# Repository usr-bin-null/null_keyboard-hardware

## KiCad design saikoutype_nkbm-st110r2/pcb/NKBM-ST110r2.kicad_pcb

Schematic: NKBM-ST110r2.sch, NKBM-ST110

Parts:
H11: SPI
H21: EXPANSION
H31: RESET
H41: VCCIN
L00, L01, L02, L03, L04, L05, L06, L07, L08, L09: LED
MCU1: Teesny2.0++; TEENSY2.0++
R00, R01, R02, R03, R04, R05, R06, R07, R08, R09: 330
USB_POWER: SOLDER_JUMPER; SOLDER_BRIDGE

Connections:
/COL_00: MCU1.31 (PF0); also elsewhere on the board
/COL_01: MCU1.30 (PF1); also elsewhere on the board
/COL_02: MCU1.29 (PF2); also elsewhere on the board
/COL_03: MCU1.28 (PF3); also elsewhere on the board
/COL_04: MCU1.27 (PF4); also elsewhere on the board
/COL_05: MCU1.26 (FP5); also elsewhere on the board
/COL_06: MCU1.25 (FP6); also elsewhere on the board
/COL_07: MCU1.24 (PF7); also elsewhere on the board
/COL_08: MCU1.13 (PC0); also elsewhere on the board
/COL_09: MCU1.14 (PC1); also elsewhere on the board
/COL_10: MCU1.15 (PC2); also elsewhere on the board
/COL_11: MCU1.16 (PC3); also elsewhere on the board
/COL_12: MCU1.17 (PC4); also elsewhere on the board
/COL_13: MCU1.18 (PC5); also elsewhere on the board
/COL_14: MCU1.19 (PC6); also elsewhere on the board
/GND: L00.1 (K), L01.1 (K), L02.1 (K), L03.1 (K), L04.1 (K), L05.1 (K), L06.1 (K), L07.1 (K), L08.1 (K), L09.1 (K), MCU1.1 (GND), MCU1.22 (GND), MCU1.33 (GND); also elsewhere on the board
/LED_00: MCU1.2 (PB7), R00.1
/LED_01: MCU1.3 (PD0), R01.1
/LED_02: MCU1.4 (PD1), R02.1
/LED_03: MCU1.41 (PB5), R03.1
/LED_04: MCU1.40 (PB4), R04.1
/LED_05: MCU1.42 (PB6), R05.1
/LED_06: MCU1.7 (PD4), R06.1
/LED_07: MCU1.8 (PD5), R07.1
/LED_08: MCU1.9 (PD6), R08.1
/LED_09: MCU1.10 (PD7), R09.1
/MISO: MCU1.39 (PB3); also elsewhere on the board
/MOSI: MCU1.38 (PB2); also elsewhere on the board
/ROW_00: MCU1.44 (PA0); also elsewhere on the board
/ROW_01: MCU1.45 (PA1); also elsewhere on the board
/ROW_02: MCU1.46 (PA2); also elsewhere on the board
/ROW_03: MCU1.47 (PA3); also elsewhere on the board
/ROW_04: MCU1.48 (PA4); also elsewhere on the board
/ROW_05: MCU1.49 (PA5); also elsewhere on the board
/ROW_06: MCU1.50 (PA6); also elsewhere on the board
/ROW_07: MCU1.51 (PA7); also elsewhere on the board
/RST: MCU1.23 (RESET); also elsewhere on the board
/RX: MCU1.5 (PD2); also elsewhere on the board
/SCLK: MCU1.37 (PB1); also elsewhere on the board
/SELECT: MCU1.36 (PB0); also elsewhere on the board
/TX: MCU1.6 (PD3); also elsewhere on the board
/VCC: MCU1.43 (VCC); also elsewhere on the board
/VCC1: MCU1.21 (VCC)
unnamed: L00.2 (A), R00.2
unnamed: L01.2 (A), R01.2
unnamed: L02.2 (A), R02.2
unnamed: L03.2 (A), R03.2
unnamed: L04.2 (A), R04.2
unnamed: L05.2 (A), R05.2
unnamed: L06.2 (A), R06.2
unnamed 161: L07.2 (A), R07.2; also elsewhere on the board
unnamed: L08.2 (A), R08.2
unnamed 163: L09.2 (A), R09.2; also elsewhere on the board
unnamed 164: MCU1.11 (PE0); also elsewhere on the board
unnamed 165: MCU1.12 (PE1); also elsewhere on the board

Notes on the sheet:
LED
DIODE
Component Orientation

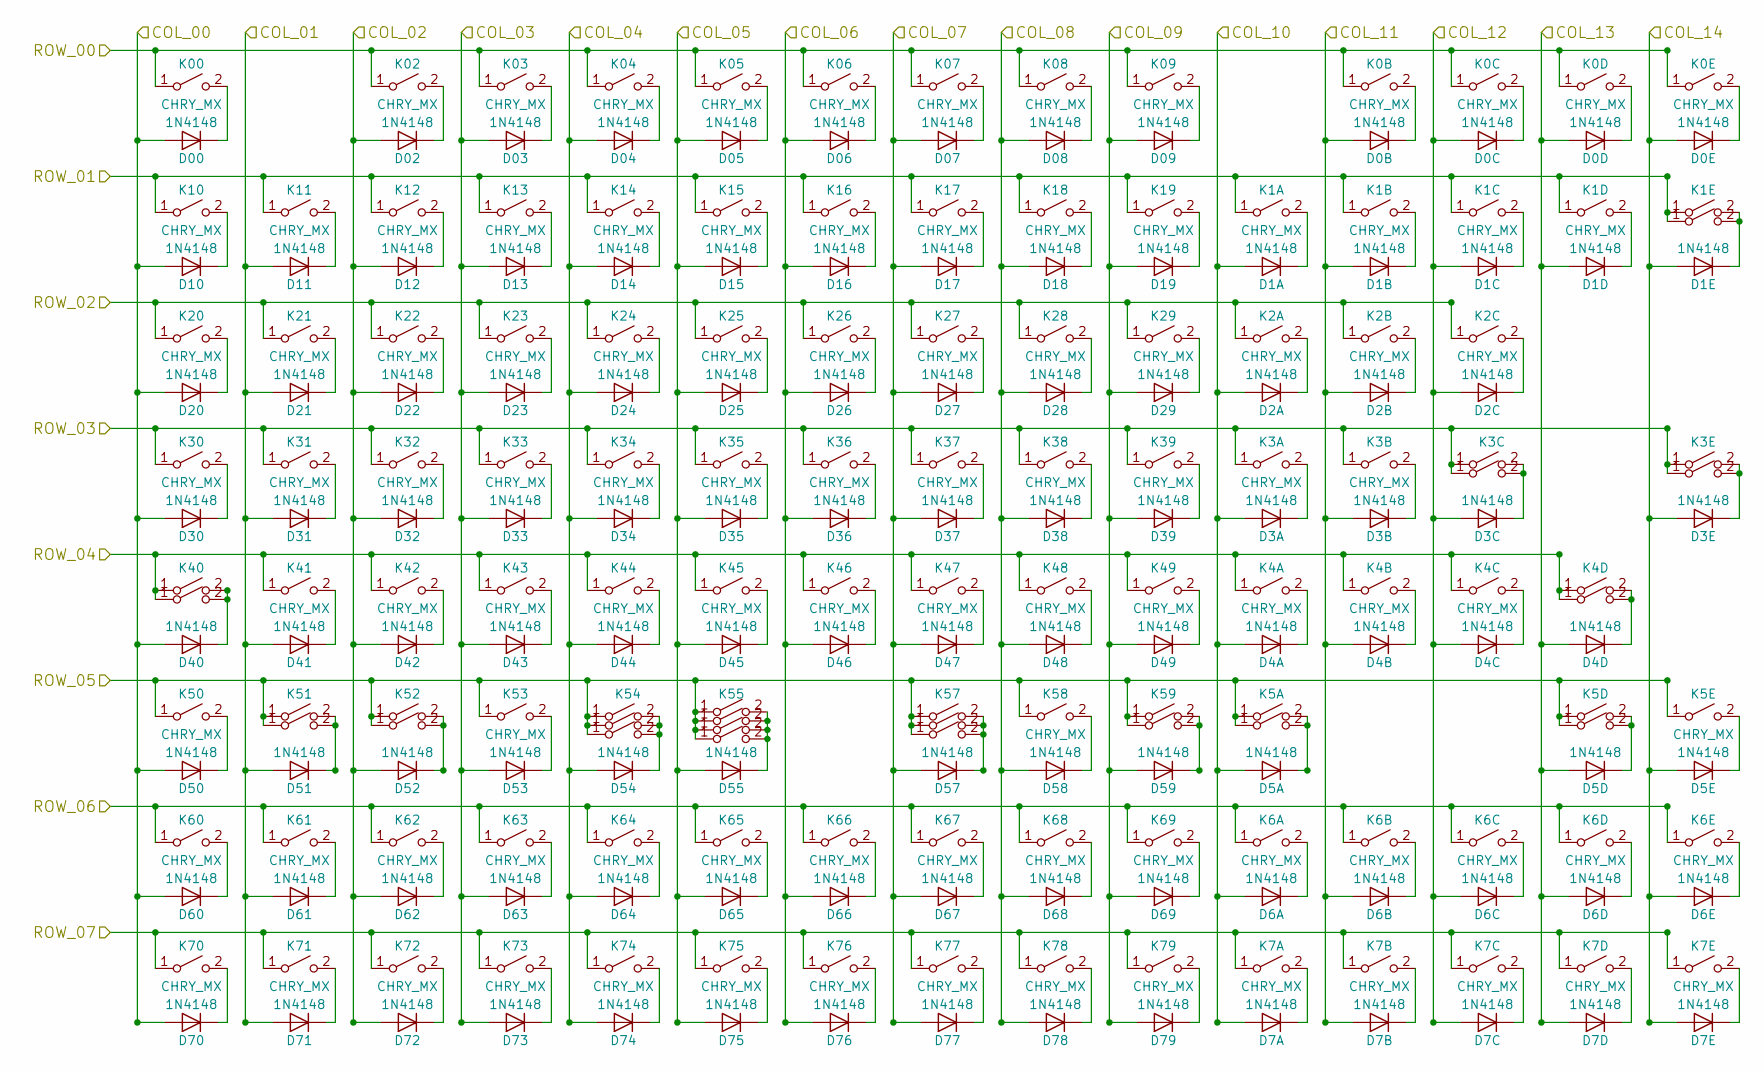
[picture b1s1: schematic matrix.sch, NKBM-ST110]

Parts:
D00, D0B, D0C, D0D, D0E, D1A, D1B, D1C, D1D, D1E, D02, D2A, D2B, D2C, D03, D3A, D3B, D3C, D3E, D04, D4A, D4B, D4C, D4D, D05, D5A, D5D, D5E, D06, D6A, D6B, D6C, D6D, D6E, D07, D7A, D7B, D7C, D7D, D7E, D08, D09, D10, D11, D12, D13, D14, D15, D16, D17, D18, D19, D20, D21, D22, D23, D24, D25, D26, D27, D28, D29, D30, D31, D32, D33, D34, D35, D36, D37, D38, D39, D40, D41, D42, D43, D44, D45, D46, D47, D48, D49, D50, D51, D52, D53, D54, D55, D57, D58, D59, D60, D61, D62, D63, D64, D65, D66, D67, D68, D69, D70, D71, D72, D73, D74, D75, D76, D77, D78, D79: 1N4148; DIODE
K00, K0B, K0C, K0D, K0E, K1A, K1B, K1C, K1D, K1E1, K02, K2A, K2B, K2C, K03, K3A, K3B, K04, K4A, K4B, K4C, K05, K5D, K06, K6A, K6B, K6C, K6D, K6E, K07, K7A, K7B, K7C, K7D, K7E, K08, K09, K10, K11, K12, K13, K14, K15, K16, K17, K18, K19, K21, K22, K23, K24, K25, K26, K27, K28, K29, K31, K32, K33, K34, K35, K36, K37, K38, K39, K41, K42, K43, K44, K46, K47, K48, K49, K51, K53, K60, K61, K62, K63, K64, K65, K66, K67, K68, K69, K70, K71, K72, K73, K74, K75, K76, K77, K78, K79: CHRY_MX; CHERRY_PLATE_100H
K1E, K3E, K54, K57: CHRY_MX; CHERRY_PLATE_200H
K3C, K3C1, K20: CHRY_MX; CHERRY_PLATE_150H
K3E1, K40, K541, K572: CHRY_MX; CHERRY_PLATE_225H
K4D, K30: CHRY_MX; CHERRY_PLATE_175H
K4D2: CHRY_MX; CHERRY_PLATE_275H
K5A, K5A1, K5D1, K5E, K45, K50, K52, K58, K59, K401, K511, K521, K542, K551, K553, K571, K591: CHRY_MX; CHERRY_PLATE_125H
K55: CHRY_MX; CHERRY_PLATE_625H
K552: CHRY_MX; CHERRY_PLATE_450H

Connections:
/COL_00: D00.2 (A), D10.2 (A), D20.2 (A), D30.2 (A), D40.2 (A), D50.2 (A), D60.2 (A), D70.2 (A); also elsewhere on the board
/COL_01: D11.2 (A), D21.2 (A), D31.2 (A), D41.2 (A), D51.2 (A), D61.2 (A), D71.2 (A); also elsewhere on the board
/COL_02: D02.2 (A), D12.2 (A), D22.2 (A), D32.2 (A), D42.2 (A), D52.2 (A), D62.2 (A), D72.2 (A); also elsewhere on the board
/COL_03: D03.2 (A), D13.2 (A), D23.2 (A), D33.2 (A), D43.2 (A), D53.2 (A), D63.2 (A), D73.2 (A); also elsewhere on the board
/COL_04: D04.2 (A), D14.2 (A), D24.2 (A), D34.2 (A), D44.2 (A), D54.2 (A), D64.2 (A), D74.2 (A); also elsewhere on the board
/COL_05: D05.2 (A), D15.2 (A), D25.2 (A), D35.2 (A), D45.2 (A), D55.2 (A), D65.2 (A), D75.2 (A); also elsewhere on the board
/COL_06: D06.2 (A), D16.2 (A), D26.2 (A), D36.2 (A), D46.2 (A), D66.2 (A), D76.2 (A); also elsewhere on the board
/COL_07: D07.2 (A), D17.2 (A), D27.2 (A), D37.2 (A), D47.2 (A), D57.2 (A), D67.2 (A), D77.2 (A); also elsewhere on the board
/COL_08: D08.2 (A), D18.2 (A), D28.2 (A), D38.2 (A), D48.2 (A), D58.2 (A), D68.2 (A), D78.2 (A); also elsewhere on the board
/COL_09: D09.2 (A), D19.2 (A), D29.2 (A), D39.2 (A), D49.2 (A), D59.2 (A), D69.2 (A), D79.2 (A); also elsewhere on the board
/COL_10: D1A.2 (A), D2A.2 (A), D3A.2 (A), D4A.2 (A), D5A.2 (A), D6A.2 (A), D7A.2 (A); also elsewhere on the board
/COL_11: D0B.2 (A), D1B.2 (A), D2B.2 (A), D3B.2 (A), D4B.2 (A), D6B.2 (A), D7B.2 (A); also elsewhere on the board
/COL_12: D0C.2 (A), D1C.2 (A), D2C.2 (A), D3C.2 (A), D4C.2 (A), D6C.2 (A), D7C.2 (A); also elsewhere on the board
/COL_13: D0D.2 (A), D1D.2 (A), D4D.2 (A), D5D.2 (A), D6D.2 (A), D7D.2 (A); also elsewhere on the board
/COL_14: D0E.2 (A), D1E.2 (A), D3E.2 (A), D5E.2 (A), D6E.2 (A), D7E.2 (A); also elsewhere on the board
/ROW_00: K00.1 (A), K0B.1 (A), K0C.1 (A), K0D.1 (A), K0E.1 (A), K02.1 (A), K03.1 (A), K04.1 (A), K05.1 (A), K06.1 (A), K07.1 (A), K08.1 (A), K09.1 (A); also elsewhere on the board
/ROW_01: K1A.1 (A), K1B.1 (A), K1C.1 (A), K1D.1 (A), K1E.1 (A), K1E1.1 (A), K10.1 (A), K11.1 (A), K12.1 (A), K13.1 (A), K14.1 (A), K15.1 (A), K16.1 (A), K17.1 (A), K18.1 (A), K19.1 (A); also elsewhere on the board
/ROW_02: K2A.1 (A), K2B.1 (A), K2C.1 (A), K20.1 (A), K21.1 (A), K22.1 (A), K23.1 (A), K24.1 (A), K25.1 (A), K26.1 (A), K27.1 (A), K28.1 (A), K29.1 (A); also elsewhere on the board
/ROW_03: K3A.1 (A), K3B.1 (A), K3C.1 (A), K3C1.1 (A), K3E.1 (A), K3E1.1 (A), K30.1 (A), K31.1 (A), K32.1 (A), K33.1 (A), K34.1 (A), K35.1 (A), K36.1 (A), K37.1 (A), K38.1 (A), K39.1 (A); also elsewhere on the board
/ROW_04: K4A.1 (A), K4B.1 (A), K4C.1 (A), K4D.1 (A), K4D2.1 (A), K40.1 (A), K41.1 (A), K42.1 (A), K43.1 (A), K44.1 (A), K45.1 (A), K46.1 (A), K47.1 (A), K48.1 (A), K49.1 (A), K401.1 (A); also elsewhere on the board
/ROW_05: K5A.1 (A), K5A1.1 (A), K5D.1 (A), K5D1.1 (A), K5E.1 (A), K50.1 (A), K51.1 (A), K52.1 (A), K53.1 (A), K54.1 (A), K55.1 (A), K57.1 (A), K58.1 (A), K59.1 (A), K511.1 (A), K521.1 (A), K541.1 (A), K542.1 (A), K551.1 (A), K552.1 (A), K553.1 (A), K571.1 (A), K572.1 (A), K591.1 (A); also elsewhere on the board
/ROW_06: K6A.1 (A), K6B.1 (A), K6C.1 (A), K6D.1 (A), K6E.1 (A), K60.1 (A), K61.1 (A), K62.1 (A), K63.1 (A), K64.1 (A), K65.1 (A), K66.1 (A), K67.1 (A), K68.1 (A), K69.1 (A); also elsewhere on the board
/ROW_07: K7A.1 (A), K7B.1 (A), K7C.1 (A), K7D.1 (A), K7E.1 (A), K70.1 (A), K71.1 (A), K72.1 (A), K73.1 (A), K74.1 (A), K75.1 (A), K76.1 (A), K77.1 (A), K78.1 (A), K79.1 (A); also elsewhere on the board
unnamed: D0B.1 (K), K0B.2 (B)
unnamed: D0C.1 (K), K0C.2 (B)
unnamed: D0D.1 (K), K0D.2 (B)
unnamed: D0E.1 (K), K0E.2 (B)
unnamed: D00.1 (K), K00.2 (B)
unnamed: D1A.1 (K), K1A.2 (B)
unnamed: D1B.1 (K), K1B.2 (B)
unnamed: D1C.1 (K), K1C.2 (B)
unnamed: D1D.1 (K), K1D.2 (B)
unnamed 52: D1E.1 (K), K1E.2 (B), K1E1.2 (B); also elsewhere on the board
unnamed: D2A.1 (K), K2A.2 (B)
unnamed: D2B.1 (K), K2B.2 (B)
unnamed: D2C.1 (K), K2C.2 (B)
unnamed: D3A.1 (K), K3A.2 (B)
unnamed: D3B.1 (K), K3B.2 (B)
unnamed 58: D3C.1 (K), K3C.2 (B), K3C1.2 (B); also elsewhere on the board
unnamed 59: D3E.1 (K), K3E.2 (B), K3E1.2 (B); also elsewhere on the board
unnamed: D4A.1 (K), K4A.2 (B)
unnamed: D4B.1 (K), K4B.2 (B)
unnamed: D4C.1 (K), K4C.2 (B)
unnamed: D4D.1 (K), K4D.2 (B), K4D2.2 (B)
unnamed: D5A.1 (K), K5A.2 (B), K5A1.2 (B)
unnamed: D5D.1 (K), K5D.2 (B), K5D1.2 (B)
unnamed: D5E.1 (K), K5E.2 (B)
unnamed: D6A.1 (K), K6A.2 (B)
unnamed: D6B.1 (K), K6B.2 (B)
unnamed: D6C.1 (K), K6C.2 (B)
unnamed: D6D.1 (K), K6D.2 (B)
unnamed: D6E.1 (K), K6E.2 (B)
unnamed: D7A.1 (K), K7A.2 (B)
unnamed: D7B.1 (K), K7B.2 (B)
unnamed: D7C.1 (K), K7C.2 (B)
unnamed: D7D.1 (K), K7D.2 (B)
unnamed: D7E.1 (K), K7E.2 (B)
unnamed: D02.1 (K), K02.2 (B)
unnamed: D03.1 (K), K03.2 (B)
unnamed: D04.1 (K), K04.2 (B)
unnamed: D05.1 (K), K05.2 (B)
unnamed: D06.1 (K), K06.2 (B)
unnamed: D07.1 (K), K07.2 (B)
unnamed: D08.1 (K), K08.2 (B)
unnamed: D09.1 (K), K09.2 (B)
unnamed: D10.1 (K), K10.2 (B)
unnamed: D11.1 (K), K11.2 (B)
unnamed: D12.1 (K), K12.2 (B)
unnamed: D13.1 (K), K13.2 (B)
unnamed: D14.1 (K), K14.2 (B)
unnamed: D15.1 (K), K15.2 (B)
unnamed: D16.1 (K), K16.2 (B)
unnamed: D17.1 (K), K17.2 (B)
unnamed: D18.1 (K), K18.2 (B)
unnamed: D19.1 (K), K19.2 (B)
unnamed: D20.1 (K), K20.2 (B)
unnamed: D21.1 (K), K21.2 (B)
unnamed: D22.1 (K), K22.2 (B)
unnamed: D23.1 (K), K23.2 (B)
unnamed: D24.1 (K), K24.2 (B)
unnamed: D25.1 (K), K25.2 (B)
unnamed: D26.1 (K), K26.2 (B)
unnamed: D27.1 (K), K27.2 (B)
unnamed: D28.1 (K), K28.2 (B)
unnamed: D29.1 (K), K29.2 (B)
unnamed: D30.1 (K), K30.2 (B)
unnamed: D31.1 (K), K31.2 (B)
unnamed: D32.1 (K), K32.2 (B)
unnamed: D33.1 (K), K33.2 (B)
unnamed: D34.1 (K), K34.2 (B)
unnamed: D35.1 (K), K35.2 (B)
unnamed: D36.1 (K), K36.2 (B)
unnamed: D37.1 (K), K37.2 (B)
unnamed: D38.1 (K), K38.2 (B)
unnamed: D39.1 (K), K39.2 (B)
unnamed 115: D40.1 (K), K40.2 (B), K401.2 (B); also elsewhere on the board
unnamed: D41.1 (K), K41.2 (B)
unnamed: D42.1 (K), K42.2 (B)
unnamed: D43.1 (K), K43.2 (B)
unnamed: D44.1 (K), K44.2 (B)
unnamed: D45.1 (K), K45.2 (B)
unnamed: D46.1 (K), K46.2 (B)
unnamed: D47.1 (K), K47.2 (B)
unnamed: D48.1 (K), K48.2 (B)
unnamed: D49.1 (K), K49.2 (B)
unnamed: D50.1 (K), K50.2 (B)
unnamed: D51.1 (K), K51.2 (B), K511.2 (B)
unnamed: D52.1 (K), K52.2 (B), K521.2 (B)
unnamed 128: D53.1 (K), K53.2 (B); also elsewhere on the board
unnamed 129: D54.1 (K), K54.2 (B), K541.2 (B), K542.2 (B); also elsewhere on the board
unnamed 130: D55.1 (K), K55.2 (B), K551.2 (B), K552.2 (B), K553.2 (B); also elsewhere on the board
unnamed 131: D57.1 (K), K57.2 (B), K571.2 (B), K572.2 (B); also elsewhere on the board
unnamed 132: D58.1 (K), K58.2 (B); also elsewhere on the board
unnamed: D59.1 (K), K59.2 (B), K591.2 (B)
unnamed: D60.1 (K), K60.2 (B)
unnamed: D61.1 (K), K61.2 (B)
unnamed: D62.1 (K), K62.2 (B)
unnamed: D63.1 (K), K63.2 (B)
unnamed: D64.1 (K), K64.2 (B)
unnamed: D65.1 (K), K65.2 (B)
unnamed: D66.1 (K), K66.2 (B)
unnamed: D67.1 (K), K67.2 (B)
unnamed: D68.1 (K), K68.2 (B)
unnamed: D69.1 (K), K69.2 (B)
unnamed: D70.1 (K), K70.2 (B)
unnamed: D71.1 (K), K71.2 (B)
unnamed: D72.1 (K), K72.2 (B)
unnamed: D73.1 (K), K73.2 (B)
unnamed: D74.1 (K), K74.2 (B)
unnamed: D75.1 (K), K75.2 (B)
unnamed: D76.1 (K), K76.2 (B)
unnamed: D77.1 (K), K77.2 (B)
unnamed: D78.1 (K), K78.2 (B)
unnamed: D79.1 (K), K79.2 (B)

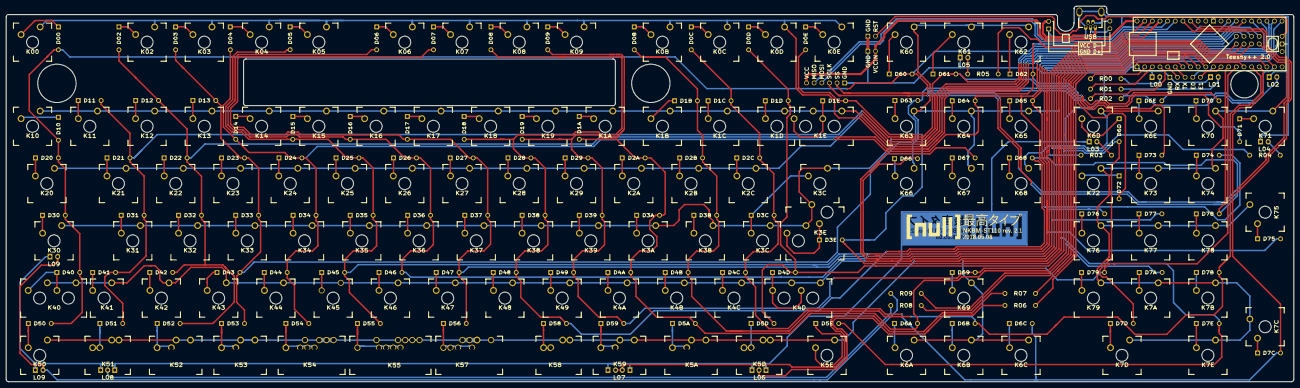
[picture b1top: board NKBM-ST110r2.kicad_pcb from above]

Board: 2 copper layers, 428.4 x 124.9 mm, 274 parts (0 on the bottom side), 165 nets.

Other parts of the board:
D56: 1N4148; DIODE
EXPANSION: HEADER; TEENSY2.0++
K1E2, K58#2: CHRY_MX; CHERRY_PLATE_100H
K3C#2: CHRY_MX; CHERRY_PLATE_150H
K3E2, K573: CHRY_MX; CHERRY_PLATE_225H
K402, K521#2, K521#3, K553#2, K572#2: CHRY_MX; CHERRY_PLATE_125H
L07#2, L09#2: LED; LED_3MM
RST: HEADER; TEENSY2.0++
SPI: HEADER; TEENSY2.0++
USB: Molex USB_Mini-B; USB_Mini-B_Lumberg_2486_01_Horizontal
USB DATA: BREAKOUT; TEENSY2.0++
USB POWER: BREAKOUT; TEENSY2.0++
VCCIN: HEADER; TEENSY2.0++

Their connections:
/COL_07: D56.2; also elsewhere on the board
/GND: EXPANSION.1, L07#2.1, L09#2.1, RST.1, SPI.6, USB.1, USB.6, USB.7, USB POWER.1, VCCIN.1; also elsewhere on the board
/MISO: SPI.2; also elsewhere on the board
/MOSI: SPI.3; also elsewhere on the board
/ROW_01: K1E2.1; also elsewhere on the board
/ROW_03: K3C#2.1, K3E2.1; also elsewhere on the board
/ROW_04: K402.1; also elsewhere on the board
/ROW_05: K58#2.1, K521#2.1, K521#3.1, K553#2.1, K572#2.1, K573.1; also elsewhere on the board
/RST: RST.2; also elsewhere on the board
/RX: EXPANSION.2; also elsewhere on the board
/SCLK: SPI.4; also elsewhere on the board
/SELECT: SPI.5; also elsewhere on the board
/TX: EXPANSION.3; also elsewhere on the board
/VCC: SPI.1, VCCIN.2; also elsewhere on the board
unnamed 52: K1E2.2; also elsewhere on the board
unnamed 58: K3C#2.2; also elsewhere on the board
unnamed 59: K3E2.2; also elsewhere on the board
unnamed 115: K402.2; also elsewhere on the board
unnamed 128: K521#2.2; also elsewhere on the board
unnamed 129: K521#3.2; also elsewhere on the board
unnamed 130: K553#2.2; also elsewhere on the board
unnamed 131: D56.1, K572#2.2, K573.2; also elsewhere on the board
unnamed 132: K58#2.2; also elsewhere on the board
unnamed 161: L07#2.2; also elsewhere on the board
unnamed 163: L09#2.2; also elsewhere on the board
unnamed 164: EXPANSION.4; also elsewhere on the board
unnamed 165: EXPANSION.5; also elsewhere on the board

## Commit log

2017-08-15 Add KiCad schematic and PCB files.
2017-08-16 Fixed solder mask over LED pads on back side of board.
2018-01-22 Added SaikouType NKBM-ST110r2
2018-02-07 Updated Schematic to be more readable.
2018-02-12 Complete reannotation of schematic and PCB.
2018-02-12 Added schematic PDF and SVG files.
2018-02-12 Updated NKBM-ST110r2 PCB
2018-04-17 Fixed typo + updated schematic with graphics.
2018-10-06 Release NKBM-ST110 r2.1 2018.05.08
